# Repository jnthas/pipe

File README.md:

# pipe
Circuit of the project called "Pirilampo Perpétuo"

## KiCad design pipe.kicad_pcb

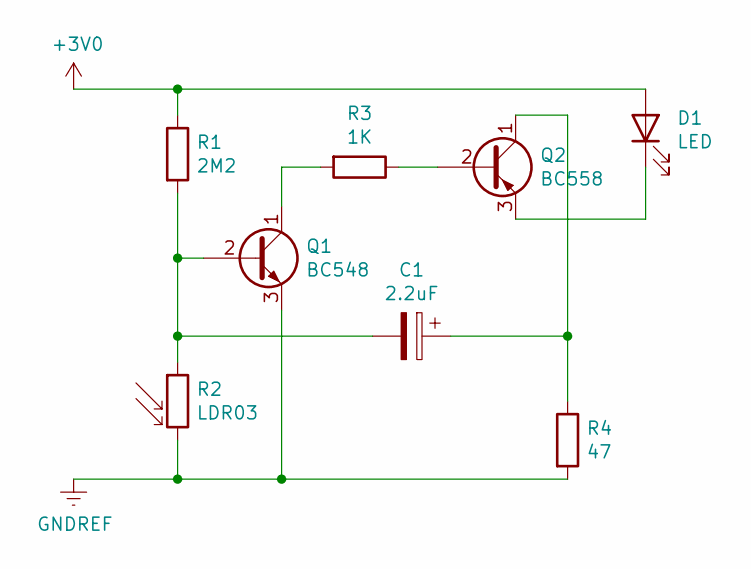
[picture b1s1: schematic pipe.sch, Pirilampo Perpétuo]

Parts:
C1: 2.2uF; CP_Radial_D5.0mm_P2.50mm
D1: LED; LED_D5.0mm
Q1: BC548; TO-92_Inline
Q2: BC558; TO-92_Inline
R1: 2M2; R_Axial_DIN0207_L6.3mm_D2.5mm_P2.54mm_Vertical
R2: LDR03; R_LDR_7x6mm_P5.1mm_Vertical
R3: 1K; R_Axial_DIN0207_L6.3mm_D2.5mm_P2.54mm_Vertical
R4: 47; R_Axial_DIN0207_L6.3mm_D2.5mm_P2.54mm_Vertical

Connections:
+3V0: D1.2 (A), R1.1
GNDREF: Q1.3 (E), R2.2, R4.2
unnamed: C1.1, Q2.1 (C), R4.1
unnamed: C1.2, Q1.2 (B), R1.2, R2.1
unnamed: D1.1 (K), Q2.3 (E)
unnamed: Q1.1 (C), R3.2
unnamed: Q2.2 (B), R3.1

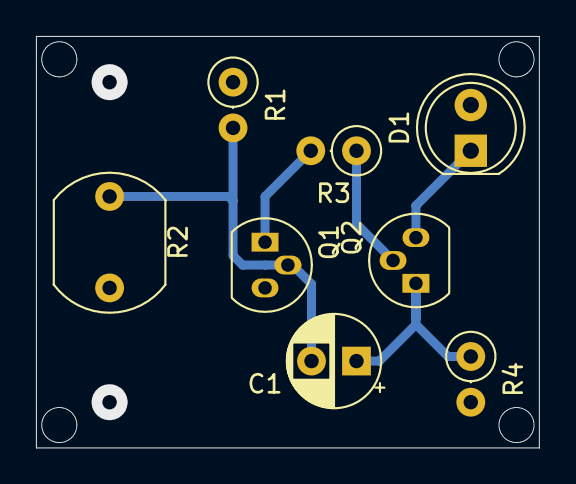
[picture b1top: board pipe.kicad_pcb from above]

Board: 2 copper layers, 27.9 x 22.9 mm, 8 parts (0 on the bottom side), 7 nets.

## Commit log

2020-12-31 add magazine
2021-01-07 Refactoring on PCB design
